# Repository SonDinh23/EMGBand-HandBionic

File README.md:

# ✋ EMGBand - Hand Bionic

<p align="center">
	<br>
	<strong>Muscle intent in → bionic motion out.</strong>   
</p>

<p align="center">
	
	&nbsp;
	
</p>

EMGBand / Hand Bionic is a full-stack, open hardware kit that turns forearm muscle signals into predictable, servo-safe hand motion. It is built to be hackable, reproducible, and fast to demo: one bill of materials, one firmware pair (ring + hand), one Flutter app to calibrate and ship.

Designed for makers, researchers, and product teams, EMGBand focuses on reliability, safety, and repeatability. The repo bundles manufacturing-ready assets (Gerbers, BOMs), production photos, a tested ESP32 firmware pair, and a Flutter app that makes calibration and demos straightforward.

## Table of Contents
- 🔍 [What this repo delivers](#what-this-repo-delivers)
- 🖼️ [Quick gallery](#quick-gallery)
- 🧭 [Platform at a glance](#platform-at-a-glance)
- ⚙️ [Architecture snapshot](#architecture-snapshot)
- 📚 [Deep dives](#deep-dives)
- 🚀 [Fast start](#fast-start)
- ✨ [Tech highlights](#tech-highlights)
- 📜 [Licence](#licence)
- 🙏 [Thanks](#thanks)

| | | |
| --- | --- | --- |
|  |  |  |

<p align="center"><sub>Wearable EMG ring + controller blocks from the latest build.</sub></p>

## What this repo delivers
- **Hardware you can fabricate**: KiCad projects for the MyoBand EMG front-end, hand controller, and modular sensor blocks. Gerbers, pick-and-place, and reference photos are ready for a quick manufacturing turn.
- **Firmware that guards the hardware**: ESP32 (ring + hand) stack with EMG filtering, intent classification, BLE services, OTA hooks, and stall-safe servo control so experiments stay repeatable and safe.
- **App that closes the loop**: Flutter client to scan, pair, stream EMG, calibrate thresholds (Line/Radar), push configs, and swap control modes without reflashing.
- **Media to build confidence**: Photos and demo videos to set assembly expectations before you order or solder.

## Quick gallery

See how the wearable comes together before diving into schematics or code.

| | | |
| --- | --- | --- |
| <br><small>📸 Assembled unit 1</small> | <br><small>📸 Assembled unit 2</small> | <br><small>📸 Assembled unit 3</small> |
| <br><small>🖼️ Side profile</small> | <br><small>🔬 Sensor block close-up</small> | <br><small>🔗 Strap view</small> |

<p align="center"><strong>Live demo videos</strong></p>
<p align="center">
	<video src="resources/video/Demo1.mp4" width="360" controls muted></video>
	<video src="resources/video/Demo2.mp4" width="360" controls muted></video>
</p>

<p align="center"><small>If embeds do not autoplay in your viewer, use the direct links: <a href="resources/video/Demo1.mp4">Demo1.mp4</a> · <a href="resources/video/Demo2.mp4">Demo2.mp4</a>.</small></p>

## Platform at a glance

| Layer | Highlights |
| --- | --- |
| 🛠️ **Hardware** | Low-noise EMG front-end, modular controller blocks, ready-to-manufacture assets, BOMs aligned to the photos you see. |
| 🧠 **Firmware** | ESP32 (ring + hand), FreeRTOS, NimBLE, OTA-ready, Line/Radar classifiers, servo current and motion guards to avoid stalls. |
| 📱 **App** | Flutter UX for BLE JSON control, half-float EMG streaming, auto pair/connect, per-user calibration, and live plots. |

## Architecture snapshot

Signal path in two stages: capture and clean EMG on the ring, classify intent and drive actuators on the hand controller. Calibration data lives in the app and syncs over BLE when you change modes.

<table>
	<tr>
		<td align="center"><br><small>⚡ Raw EMG capture</small></td>
			<td align="center"><br><small>🔎 Line thresholds</small></td>
			<td align="center"><br><small>🔁 Radar/Spider matching</small></td>
	</tr>
	<tr>
		<td align="center"><br><small>✅ Match confidence</small></td>
		<td align="center"><br><small>➖ Similarity metric</small></td>
		<td align="center"><br><small>📱 Flutter app in action</small></td>
	</tr>
</table>

## Deep dives
- Hardware overview, IC map, and board variants: [hardware/README.md](hardware/README.md)
- Firmware flow, EMG filters/classifiers, BLE/OTA services: [firmware/README.md](firmware/README.md)
- App BLE flows, JSON protocol, half-float decode, and UI cues: [app/README.md](app/README.md)

## Fast start
1) **Fabricate / assemble**: pick your board set from [hardware](hardware/README.md); use the included Gerbers and assembly files to keep builds consistent with the photos.
2) **Flash firmware**: open `firmware/Embedded` in VS Code + PlatformIO, select the target (ring/hand), and run `pio run -t upload`.
3) **Pair with the app**: run the Flutter app (see [app/README.md](app/README.md)), scan and save Hand + MyoBand, then start EMG streaming.
4) **Calibrate deliberately**: choose Line or Radar, adjust thresholds/templates, push to devices, and watch the live plots to confirm stability.
5) **Demo safely**: use the stall/over-activity protections while you tune grip strength or motion ranges.

## Tech highlights
- Half-precision EMG streaming keeps BLE lean; float32 reconstruction happens in the app for analysis.
- Dual control modes: Line (summed thresholds for fast response) and Radar/Spider (template similarity, ≥70% match) for finer intent mapping.
- Safety nets: relax-before-use gating, over-activity clamps, current-based stall detection on servos, watchdog-backed tasks, and OTA hooks for quick fixes.
- UX polish: LED/buzzer cues, auto reconnect, smoothed charts, per-grip calibration profiles, and JSON-based control that is easy to script.

## Licence

This project is licensed under the GNU GPLv3.  
Compared to permissive licences like MIT, GPLv3 requires that if you modify this code and distribute your version (including in commercial products), you must also release your changes under the same GPLv3 licence and provide the corresponding source code.  

This way, everyone can benefit from improvements built on top of this project.  
If this licence causes issues for your intended use, feel free to contact me – I’m open to discussing alternatives.

## Thanks

Huge thanks to contributors, early testers, and the open-source toolchains that made this build possible. Enjoy hacking, and share what you build.

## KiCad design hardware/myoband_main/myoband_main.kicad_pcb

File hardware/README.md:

# 🔧 Hardware Reference

The definitive pit stop for every PCB in the EMGBand/Hand Bionic stack. Each section tells you what the board does, how it talks to the rest, where to grab build assets, and what to check before you power it up—plus a gallery pulled straight from the committed files.

## 📌 At-a-glance

| Board | Role | Primary interfaces | Manufacturing kit |
| --- | --- | --- | --- |
| [Hand_main](#hand_main) | Bionic hand controller, Wi-Fi/BLE, power/rail monitor | USB-C, UART, GPIO, RGB LED | `Hand_main/*.kicad_*`, top/bottom photos |
| [myoband_main](#myoband_main) | Wearable hub for EMG/IMU/mic, power + comms | USB-UART, Wi-Fi/BLE, SPI/I2C/I2S, ADC | `myoband_main/*.kicad_*`, top/bottom photos |
| [myoBand_emg](#myoBand_emg) | EMG front-end with INA333 multi-stage filtering | Differential electrodes → analog out | `myoBand_emg/*.kicad_*`, top/bottom photos |
| [myoBand_emg_Renesas v0.2](#myoBand_emg_renesas-v02) | EMG front-end using ISL28533 | Differential electrodes → analog out | `myoBand_emg_Renesas/myoBand_emg_v0_2/*.kicad_*` |
| [myoBand_emg_Simulation](#myoBand_emg_simulation) | EMG filter/response simulation | N/A (SPICE) | `myoBand_emg_Simulation/*.kicad_*` |

---

## 🧠 Hand_main

### Highlights
- ESP32-WROOM-32D brain with Wi-Fi/BLE and a status RGB LED to keep you informed at a glance.
- INA3221 keeps eyes on three rails, so servos and external loads stay within safe current/voltage envelopes.
- TPS54620 buck + XC6220 LDO make clean rails; CP2102N USB–UART streamlines flashing and debug.

### Quick specs

| Parameter | Detail |
| --- | --- |
| MCU | ESP32-WROOM-32D |
| Power | Buck 5V→system, 3V3 LDO |
| Power monitor | INA3221 (3 channels) |
| Interfaces | USB-C/CP2102N, GPIO headers, WS2812 data |

### Manufacturing files
- [Hand_main/Hand_main.kicad_sch](Hand_main/Hand_main.kicad_sch)
- [Hand_main/Hand_main.kicad_pcb](Hand_main/Hand_main.kicad_pcb)
- [Hand_main/Hand_main.pdf](Hand_main/Hand_main.pdf)

### Build & test checklist
- Double-check buck polarity and place L/C exactly as laid out to keep EMI tame.
- Probe buck and 3V3 rails before seating the ESP32 or any sensitive loads.
- Confirm USB-C orientation/UART lines, then sanity-check INA3221 readings with a dummy load.

### Gallery

<table>
	<tr>
		<td align="center"><br><small>Top — overview</small></td>
		<td align="center"><br><small>Top — ESP32 & power</small></td>
	</tr>
	<tr>
		<td align="center"><br><small>Bottom — routing</small></td>
		<td align="center"><br><small>Bottom — pours</small></td>
	</tr>
</table>

---

## 🧭 myoband_main

### Highlights
- ESP32-PICO-V3-02 wearable hub that ingests EMG (MCP3208), IMU data (LSM6DSL), and PDM audio (INMP441).
- Power spine: TP4056 Li-ion charger, 3V3 LDO for logic, TPS60402 negative rail for the analog front-end.
- CP2102N handles flashing/debug; WS2812B-2020 signals state; headers expose SPI/I2C/I2S for expansions.

### Quick specs

| Parameter | Detail |
| --- | --- |
| MCU | ESP32-PICO-V3-02 |
| EMG conversion | MCP3208 (12-bit SPI) |
| Sensors | IMU LSM6DSL, mic INMP441 |
| Power | TP4056 charger, 3V3 LDO, TPS60402 negative rail |
| Interfaces | Wi-Fi/BLE, USB-UART, SPI/I2C/I2S, GPIO |

### Manufacturing files
- [myoband_main/myoband_main.kicad_sch](myoband_main/myoband_main.kicad_sch)
- [myoband_main/myoband_main.kicad_pcb](myoband_main/myoband_main.kicad_pcb)
- [myoband_main/myoband_main.pdf](myoband_main/myoband_main.pdf)

### Build & test checklist
- Inspect TP4056 charge path and battery polarity; watch thermals at higher charge currents.
- Verify the TPS60402 negative rail before biasing the EMG analog stage.
- Smoke-test everything together: Wi-Fi/BLE, SPI EMG ADC, I2C IMU, PDM mic—and listen for noise coupling.

### Gallery

<table>
	<tr>
		<td align="center"><br><small>Top — overview</small></td>
		<td align="center"><br><small>Top — MCU & IO</small></td>
		<td align="center"><br><small>Top — power/charger</small></td>
	</tr>
	<tr>
		<td align="center"><br><small>Bottom — routing</small></td>
		<td align="center"><br><small>Bottom — pours</small></td>
		<td align="center"><br><small>Bottom — placement</small></td>
	</tr>
</table>

---

## 🩺 myoBand_emg (INA333)

### Highlights
- INA333-based EMG front-end for low-noise differential gain, feeding MCP601 stages for band-pass/notch shaping.
- TPS60402 negative rail preserves headroom and keeps distortion low at higher amplitudes.
- Layout favors short electrode runs and clean analog planes away from digital chatter.

### Quick specs

| Parameter | Detail |
| --- | --- |
| Instrumentation amp | INA333 |
| Filter op-amp | MCP601 (multi-stage) |
| Power | Negative rail via TPS60402, bias/offset via R/C network |
| Output | Analog to ADC (e.g., MCP3208 on myoband_main) |

### Manufacturing files
- [myoBand_emg/EMG_SENSOR.kicad_sch](myoBand_emg/EMG_SENSOR.kicad_sch)
- [myoBand_emg/EMG_SENSOR.kicad_pcb](myoBand_emg/EMG_SENSOR.kicad_pcb)
- [myoBand_emg/EMG_SENSOR.pdf](myoBand_emg/EMG_SENSOR.pdf)

### Build & test checklist
- Match R/C values to your target corners; confirm INA333 orientation and gain resistors.
- Measure the negative rail before attaching electrodes; verify mid-bias to avoid clipping.
- Characterize baseline noise; notch the mains band or add ferrites if hum shows up.

### Gallery

<table>
	<tr>
		<td align="center"><br><small>Top — overview</small></td>
		<td align="center"><br><small>Top — amp/filter</small></td>
	</tr>
	<tr>
		<td align="center"><br><small>Bottom — routing</small></td>
		<td align="center"><br><small>Bottom — pours</small></td>
	</tr>
</table>

---

## 🩺 myoBand_emg_Renesas v0.2 (ISL28533)

### Highlights
- Renesas ISL28533 variant for a broader dynamic range and lower noise floor.
- MCP601 stack still handles staged gain and filtering; rails/bias come from the hub via R/C network.
- Same disciplined layout: short electrode routes, isolated analog plane, test-points where you need them.

### Quick specs

| Parameter | Detail |
| --- | --- |
| Instrumentation amp | ISL28533 |
| Filter op-amp | MCP601 |
| Power | Rails/bias from hub or external (no onboard charge pump) |
| Output | Analog to hub ADC |

### Manufacturing files
- [myoBand_emg_Renesas/myoBand_emg_v0_2/myoBand_emg_v0_2.kicad_sch](myoBand_emg_Renesas/myoBand_emg_v0_2/myoBand_emg_v0_2.kicad_sch)
- [myoBand_emg_Renesas/myoBand_emg_v0_2/myoBand_emg_v0_2.kicad_pcb](myoBand_emg_Renesas/myoBand_emg_v0_2/myoBand_emg_v0_2.kicad_pcb)
- [myoBand_emg_Renesas/myoBand_emg_v0_2/myoBand_emg_v0_2.pdf](myoBand_emg_Renesas/myoBand_emg_v0_2/myoBand_emg_v0_2.pdf)

### Build & test checklist
- Validate mid-rail bias when powered from the hub; confirm ISL28533 headroom at your chosen gain.
- A/B noise against the INA333 build to choose the production winner.
- Drop in renders/photos once assembled to lock placement confidence.

### Gallery
- No images in this folder yet; drop in PNG/JPG renders or photos when ready.

---

## 🧪 myoBand_emg_Simulation

### Highlights
- SPICE sandbox to shape EMG gain and filter response before you spend copper.
- Ideal sources and R/C only—no production silicon here.

### Quick specs

| Parameter | Detail |
| --- | --- |
| Purpose | Frequency/gain/notch simulation |
| Components | Ideal sources, R/C |
| Output | Simulated waveforms |

### Files
- [myoBand_emg_Simulation/myoBand_emg_Simulation.kicad_sch](myoBand_emg_Simulation/myoBand_emg_Simulation.kicad_sch)
- [myoBand_emg_Simulation/myoBand_emg_Simulation.kicad_pcb](myoBand_emg_Simulation/myoBand_emg_Simulation.kicad_pcb)

---

## 🖼️ Image & path guidance

- Use forward slashes `/` in image paths; links are relative to this README.
- Example: ``.
- GitHub renders images once the PNG files are present; add new renders/photos in the matching board folder.
- Prefer per-board READMEs or a PDF gallery? Say the word and we will scaffold it.

---

_Last refreshed: check git history for the latest author/date._

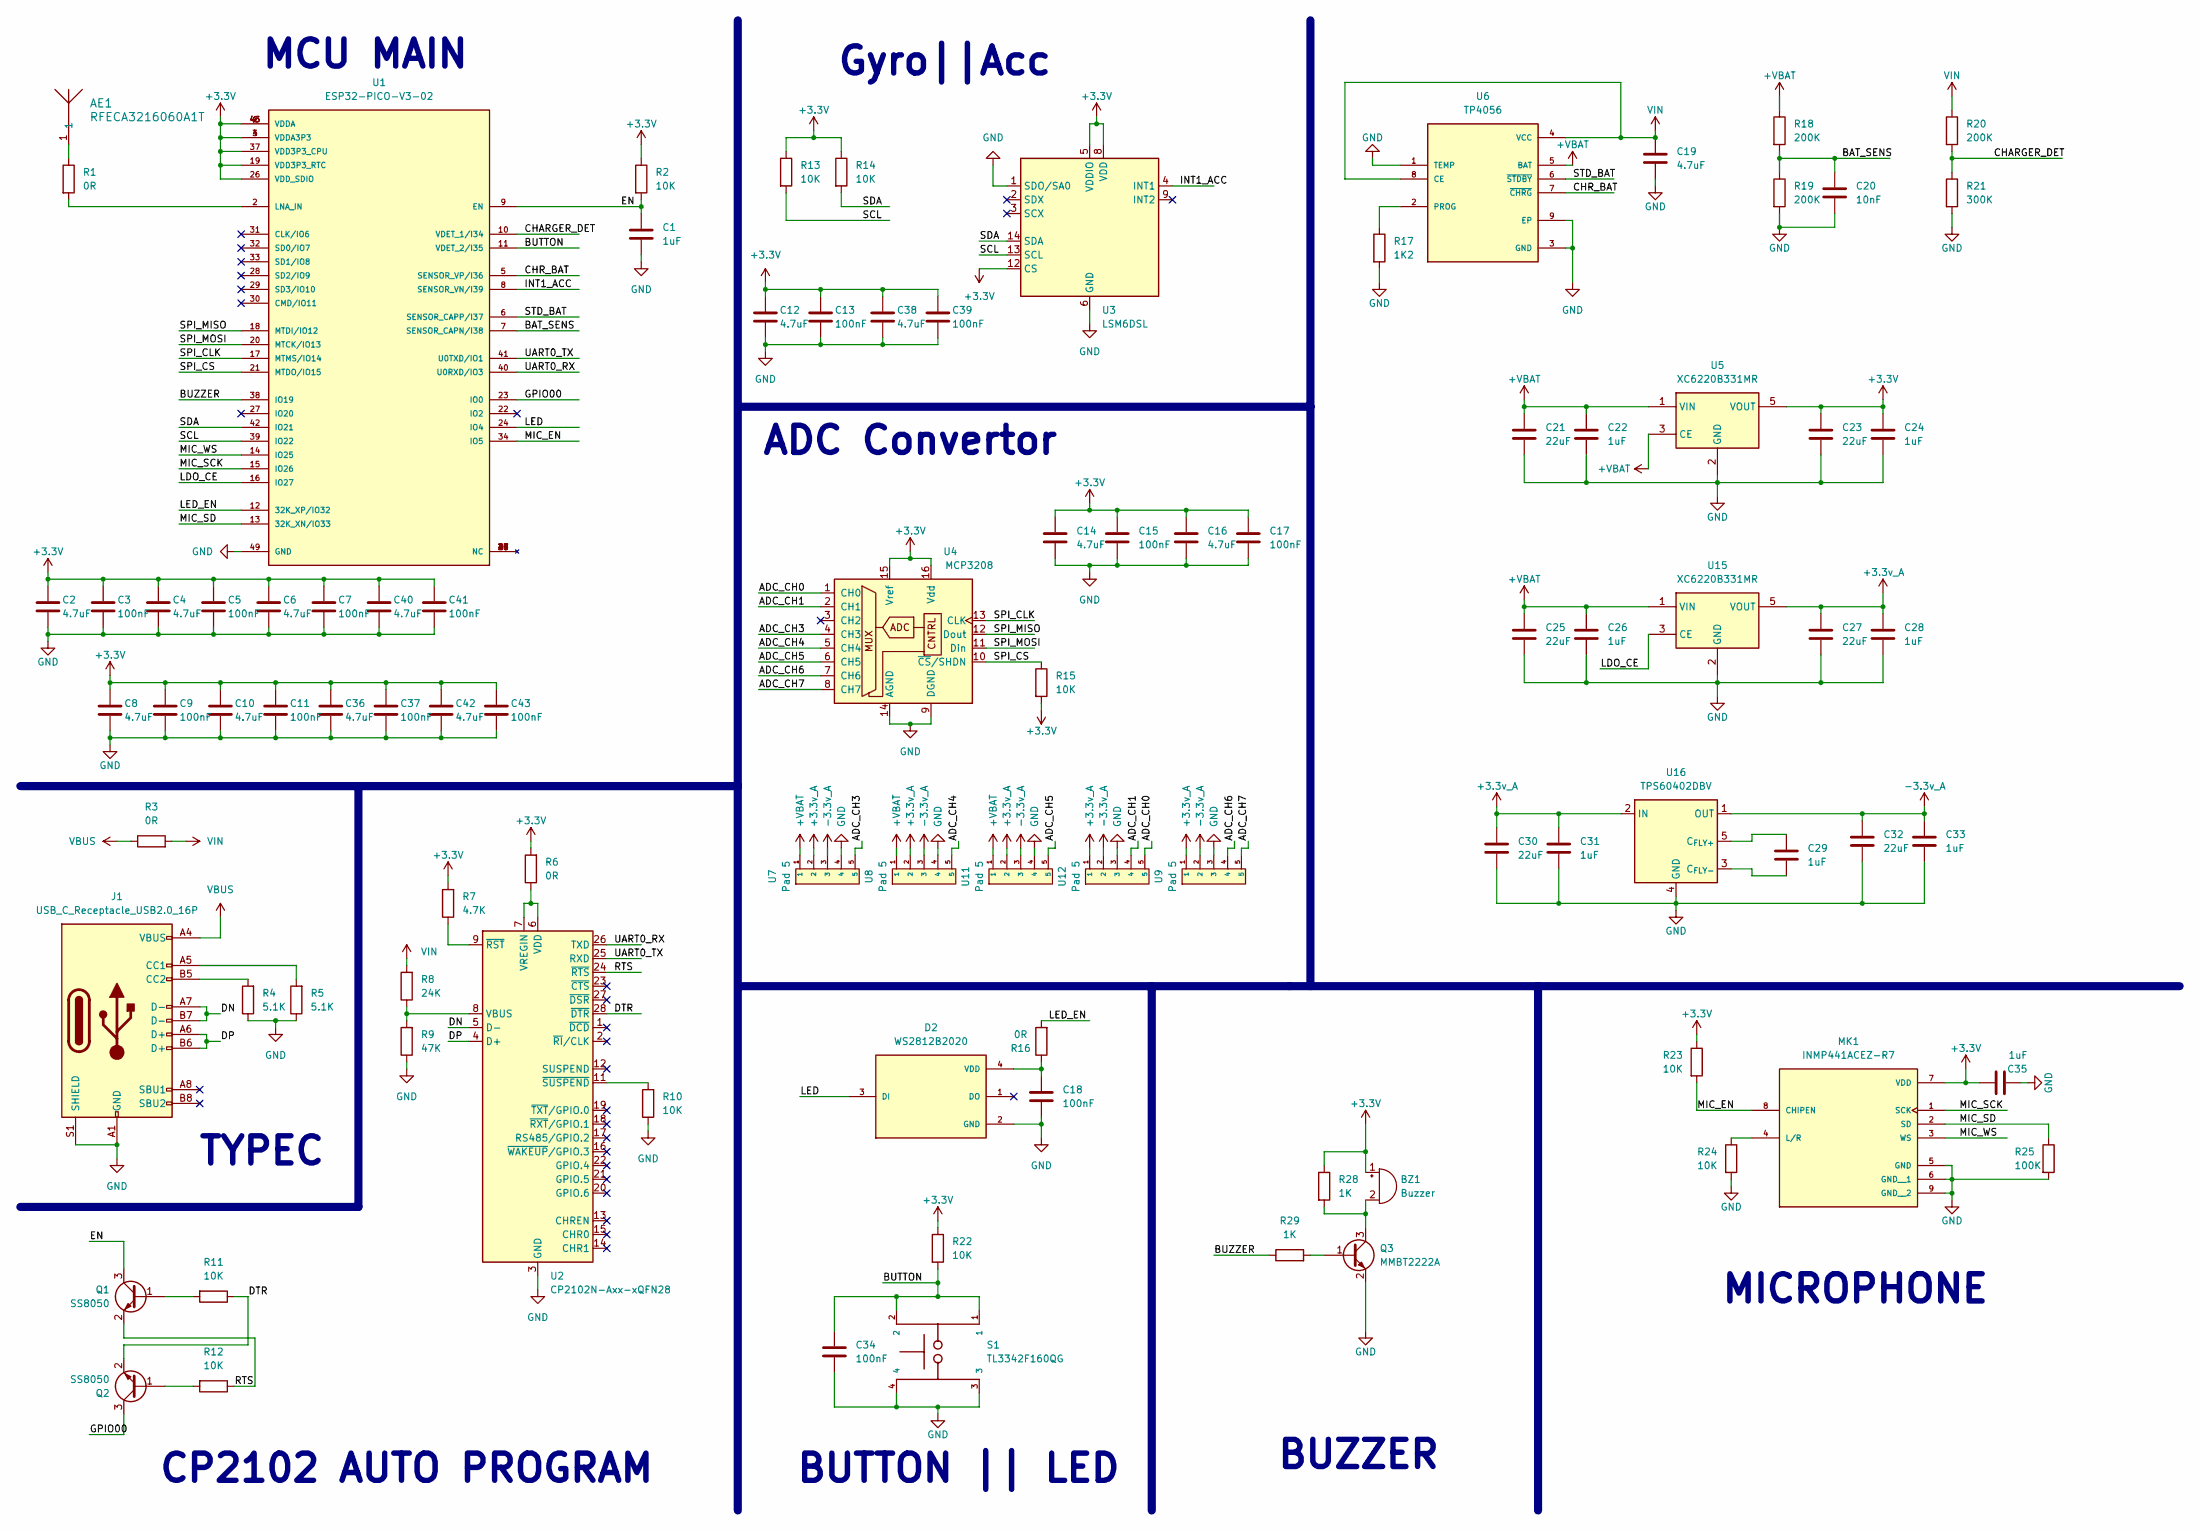
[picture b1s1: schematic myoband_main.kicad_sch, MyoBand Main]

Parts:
AE1: RFECA3216060A1T; ANT_16060A1T_WAL
BZ1: Buzzer; Buzzer_Murata_PKMCS0909E
C1, C22, C24, C26, C28, C29, C31, C33, C35: 1uF; C_0402_1005Metric
C2, C4, C6, C8, C10, C12, C14, C16, C19, C36, C38, C40, C42: 4.7uF; C_0402_1005Metric
C3, C5, C7, C9, C11, C13, C15, C17, C18, C34, C37, C39, C41, C43: 100nF; C_0402_1005Metric
C20: 10nF; C_0402_1005Metric
C21, C23, C25, C27, C30, C32: 22uF; C_0603_1608Metric
D2: WS2812B2020; LED_WS2812B2020; PARTREV V1.0
J1: USB_C_Receptacle_USB2.0_16P; USB_C_Receptacle_GCT_USB4105-xx-A_16P_TopMnt_Horizontal
MK1: INMP441ACEZ-R7; MIC_INMP441ACEZ-R7; PARTREV 1.1
Q1, Q2: SS8050; SOT-23
Q3: MMBT2222A; SOT-23
R1, R3, R6, R16: 0R; C_0402_1005Metric
R2, R10, R11, R12, R13, R14, R15, R22, R23, R24: 10K; C_0402_1005Metric
R4, R5: 5.1K; C_0402_1005Metric
R7: 4.7K; C_0402_1005Metric
R8: 24K; C_0402_1005Metric
R9: 47K; C_0402_1005Metric
R17: 1K2; C_0402_1005Metric
R18, R19, R20: 200K; C_0402_1005Metric
R21: 300K; C_0402_1005Metric
R25: 100K; C_0402_1005Metric
R28, R29: 1K; C_0402_1005Metric
S1: TL3342F160QG; SW_TL3342F160QG
U1: ESP32-PICO-V3-02; XCVR_ESP32-PICO-V3-02; PARTREV 1.0
U2: CP2102N-Axx-xQFN28; QFN-28-1EP_5x5mm_P0.5mm_EP3.35x3.35mm
U3: LSM6DSL; LGA-14_3x2.5mm_P0.5mm_LayoutBorder3x4y
U4: MCP3208; SOIC-16_3.9x9.9mm_P1.27mm
U5, U15: XC6220B331MR; SOT-23-5
U6: TP4056; SOP127P600X175-9N
U7, U8, U9, U11, U12: Pad 5
U16: TPS60402DBV; SOT-23-5

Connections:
+3.3V: BZ1.1 (+), C2.1, C3.1, C4.1, C5.1, C6.1, C7.1, C8.1, C9.1, C10.1, C11.1, C12.1, C13.1, C14.1, C15.1, C16.1, C17.1, C23.1, C24.1, C35.1, C36.1, C37.1, C38.1, C39.1, C40.1, C41.1, C42.1, C43.1, MK1.7 (VDD), R2.1, R6.2, R7.2, R13.1, R14.1, R15.2, R22.1, R23.1, R28.1, U1.1 (VDDA), U1.3 (VDDA3P3), U1.4 (VDDA3P3), U1.19 (VDD3P3_RTC), U1.26 (VDD_SDIO), U1.37 (VDD3P3_CPU), U1.43 (VDDA), U1.46 (VDDA), U3.5 (VDDIO), U3.8 (VDD), U3.12 (CS), U4.15 (Vref), U4.16 (Vdd), U5.5 (VOUT)
+3.3v_A: C27.1, C28.1, C30.1, C31.1, U7.2, U8.2, U9.1, U11.2, U12.1, U15.5 (VOUT), U16.2 (IN)
+VBAT: C21.1, C22.1, C25.1, C26.1, R18.1, U5.1 (VIN), U5.3 (CE), U6.5 (BAT), U7.1, U8.1, U11.1, U15.1 (VIN)
-3.3v_A: C32.1, C33.1, U7.3, U8.3, U9.2, U11.3, U12.2, U16.1 (OUT)
/ADC_CH0: U4.1 (CH0), U12.5
/ADC_CH1: U4.2 (CH1), U12.4
/ADC_CH3: U4.4 (CH3), U7.5
/ADC_CH4: U4.5 (CH4), U8.5
/ADC_CH5: U4.6 (CH5), U11.5
/ADC_CH6: U4.7 (CH6), U9.4
/ADC_CH7: U4.8 (CH7), U9.5
/BAT_SENS: C20.1, R18.2, R19.1, U1.7 (SENSOR_CAPN/I38)
/BUTTON: C34.1, R22.2, S1.1, S1.2, U1.11 (VDET_2/I35)
/BUZZER: R29.1, U1.38 (IO19)
/CHARGER_DET: R20.2, R21.1, U1.10 (VDET_1/I34)
/CHR_BAT: U1.5 (SENSOR_VP/I36), U6.7 (~CHRG)
/DN: J1.A7 (D-), J1.B7 (D-), U2.5 (D-)
/DP: J1.A6 (D+), J1.B6 (D+), U2.4 (D+)
/DTR: Q2.2 (E), R11.1, U2.28 (~DTR)
/EN: C1.1, Q1.3 (C), R2.2, U1.9 (EN)
/GPIO00: Q2.3 (C), U1.23 (IO0)
/INT1_ACC: U1.8 (SENSOR_VN/I39), U3.4 (INT1)
/LDO_CE: U1.16 (IO27), U15.3 (CE)
/LED: D2.3 (DI), U1.24 (IO4)
/LED_EN: R16.2, U1.12 (32K_XP/IO32)
/MIC_EN: MK1.8 (CHIPEN), R23.2, U1.34 (IO5)
/MIC_SCK: MK1.1 (SCK), U1.15 (IO26)
/MIC_SD: MK1.2 (SD), R25.1, U1.13 (32K_XN/IO33)
/MIC_WS: MK1.3 (WS), U1.14 (IO25)
/RTS: Q1.2 (E), R12.1, U2.24 (~RTS)
/SCL: R13.2, U1.39 (IO22), U3.13 (SCL)
/SDA: R14.2, U1.42 (IO21), U3.14 (SDA)
/SPI_CLK: U1.17 (MTMS/IO14), U4.13 (CLK)
/SPI_CS: R15.1, U1.21 (MTDO/IO15), U4.10 (~CS/SHDN)
/SPI_MISO: U1.18 (MTDI/IO12), U4.12 (Dout)
/SPI_MOSI: U1.20 (MTCK/IO13), U4.11 (Din)
/STD_BAT: U1.6 (SENSOR_CAPP/I37), U6.6 (~STDBY)
/UART0_RX: U1.40 (U0RXD/IO3), U2.26 (TXD)
/UART0_TX: U1.41 (U0TXD/IO1), U2.25 (RXD)
GND: C1.2, C2.2, C3.2, C4.2, C5.2, C6.2, C7.2, C8.2, C9.2, C10.2, C11.2, C12.2, C13.2, C14.2, C15.2, C16.2, C17.2, C18.2, C19.2, C20.2, C21.2, C22.2, C23.2, C24.2, C25.2, C26.2, C27.2, C28.2, C30.2, C31.2, C32.2, C33.2, C34.2, C35.2, C36.2, C37.2, C38.2, C39.2, C40.2, C41.2, C42.2, C43.2, D2.2 (GND), J1.A1 (GND), J1.A12 (GND), J1.B1 (GND), J1.B12 (GND), J1.S1 (SHIELD), MK1.5 (GND), MK1.6 (GND__1), MK1.9 (GND__2), Q3.2 (E), R4.1, R5.1, R9.1, R10.1, R17.2, R19.2, R21.2, R24.2, R25.2, S1.3, S1.4, U1.49 (GND), U2.3 (GND), U2.29 (GND), U3.1 (SDO/SA0), U3.6 (GND), U3.7 (GND), U4.9 (DGND), U4.14 (AGND), U5.2 (GND), U6.1 (TEMP), U6.3 (GND), U6.9 (EP), U7.4, U8.4, U9.3, U11.4, U12.3, U15.2 (GND), U16.4 (GND)
unnamed: AE1.1, R1.1
unnamed: BZ1.2 (-), Q3.3 (C), R28.2
unnamed: C18.1, D2.4 (VDD), R16.1
unnamed: J1.A5 (CC1), R5.2
unnamed: J1.B5 (CC2), R4.2
unnamed: MK1.4 (L/R), R24.1
unnamed: Q1.1 (B), R11.2
unnamed: Q2.1 (B), R12.2
unnamed: Q3.1 (B), R29.2
unnamed: R1.2, U1.2 (LNA_IN)
unnamed: R8.1, R9.2, U2.8 (VBUS)
unnamed: R6.1, U2.6 (VDD), U2.7 (VREGIN)
unnamed: R7.1, U2.9 (~RST)
unnamed: R10.2, U2.11 (~SUSPEND)
unnamed: R17.1, U6.2 (PROG)
unnamed: C29.1, U16.5 (C_{FLY+})
unnamed: C29.2, U16.3 (C_{FLY-})
VBUS: J1.A4 (VBUS), J1.A9 (VBUS), J1.B4 (VBUS), J1.B9 (VBUS), R3.1
VIN: C19.1, R3.2, R8.2, R20.1, U6.4 (VCC), U6.8 (CE)

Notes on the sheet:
MCU MAIN
TYPEC
BUTTON || LED
Gyro||Acc
MICROPHONE
CP2102 AUTO PROGRAM
BUZZER
ADC Convertor

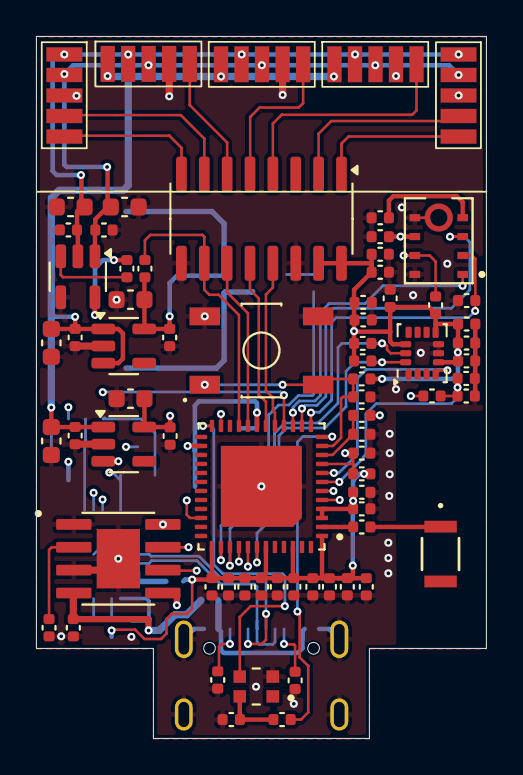
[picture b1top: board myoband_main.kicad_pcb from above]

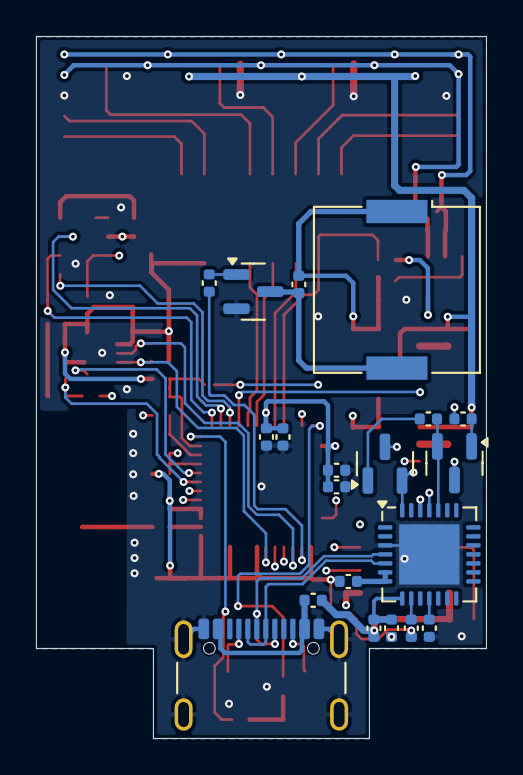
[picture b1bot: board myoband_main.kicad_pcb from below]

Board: 4 copper layers, 25.0 x 39.0 mm, 92 parts (20 on the bottom side), 59 nets.

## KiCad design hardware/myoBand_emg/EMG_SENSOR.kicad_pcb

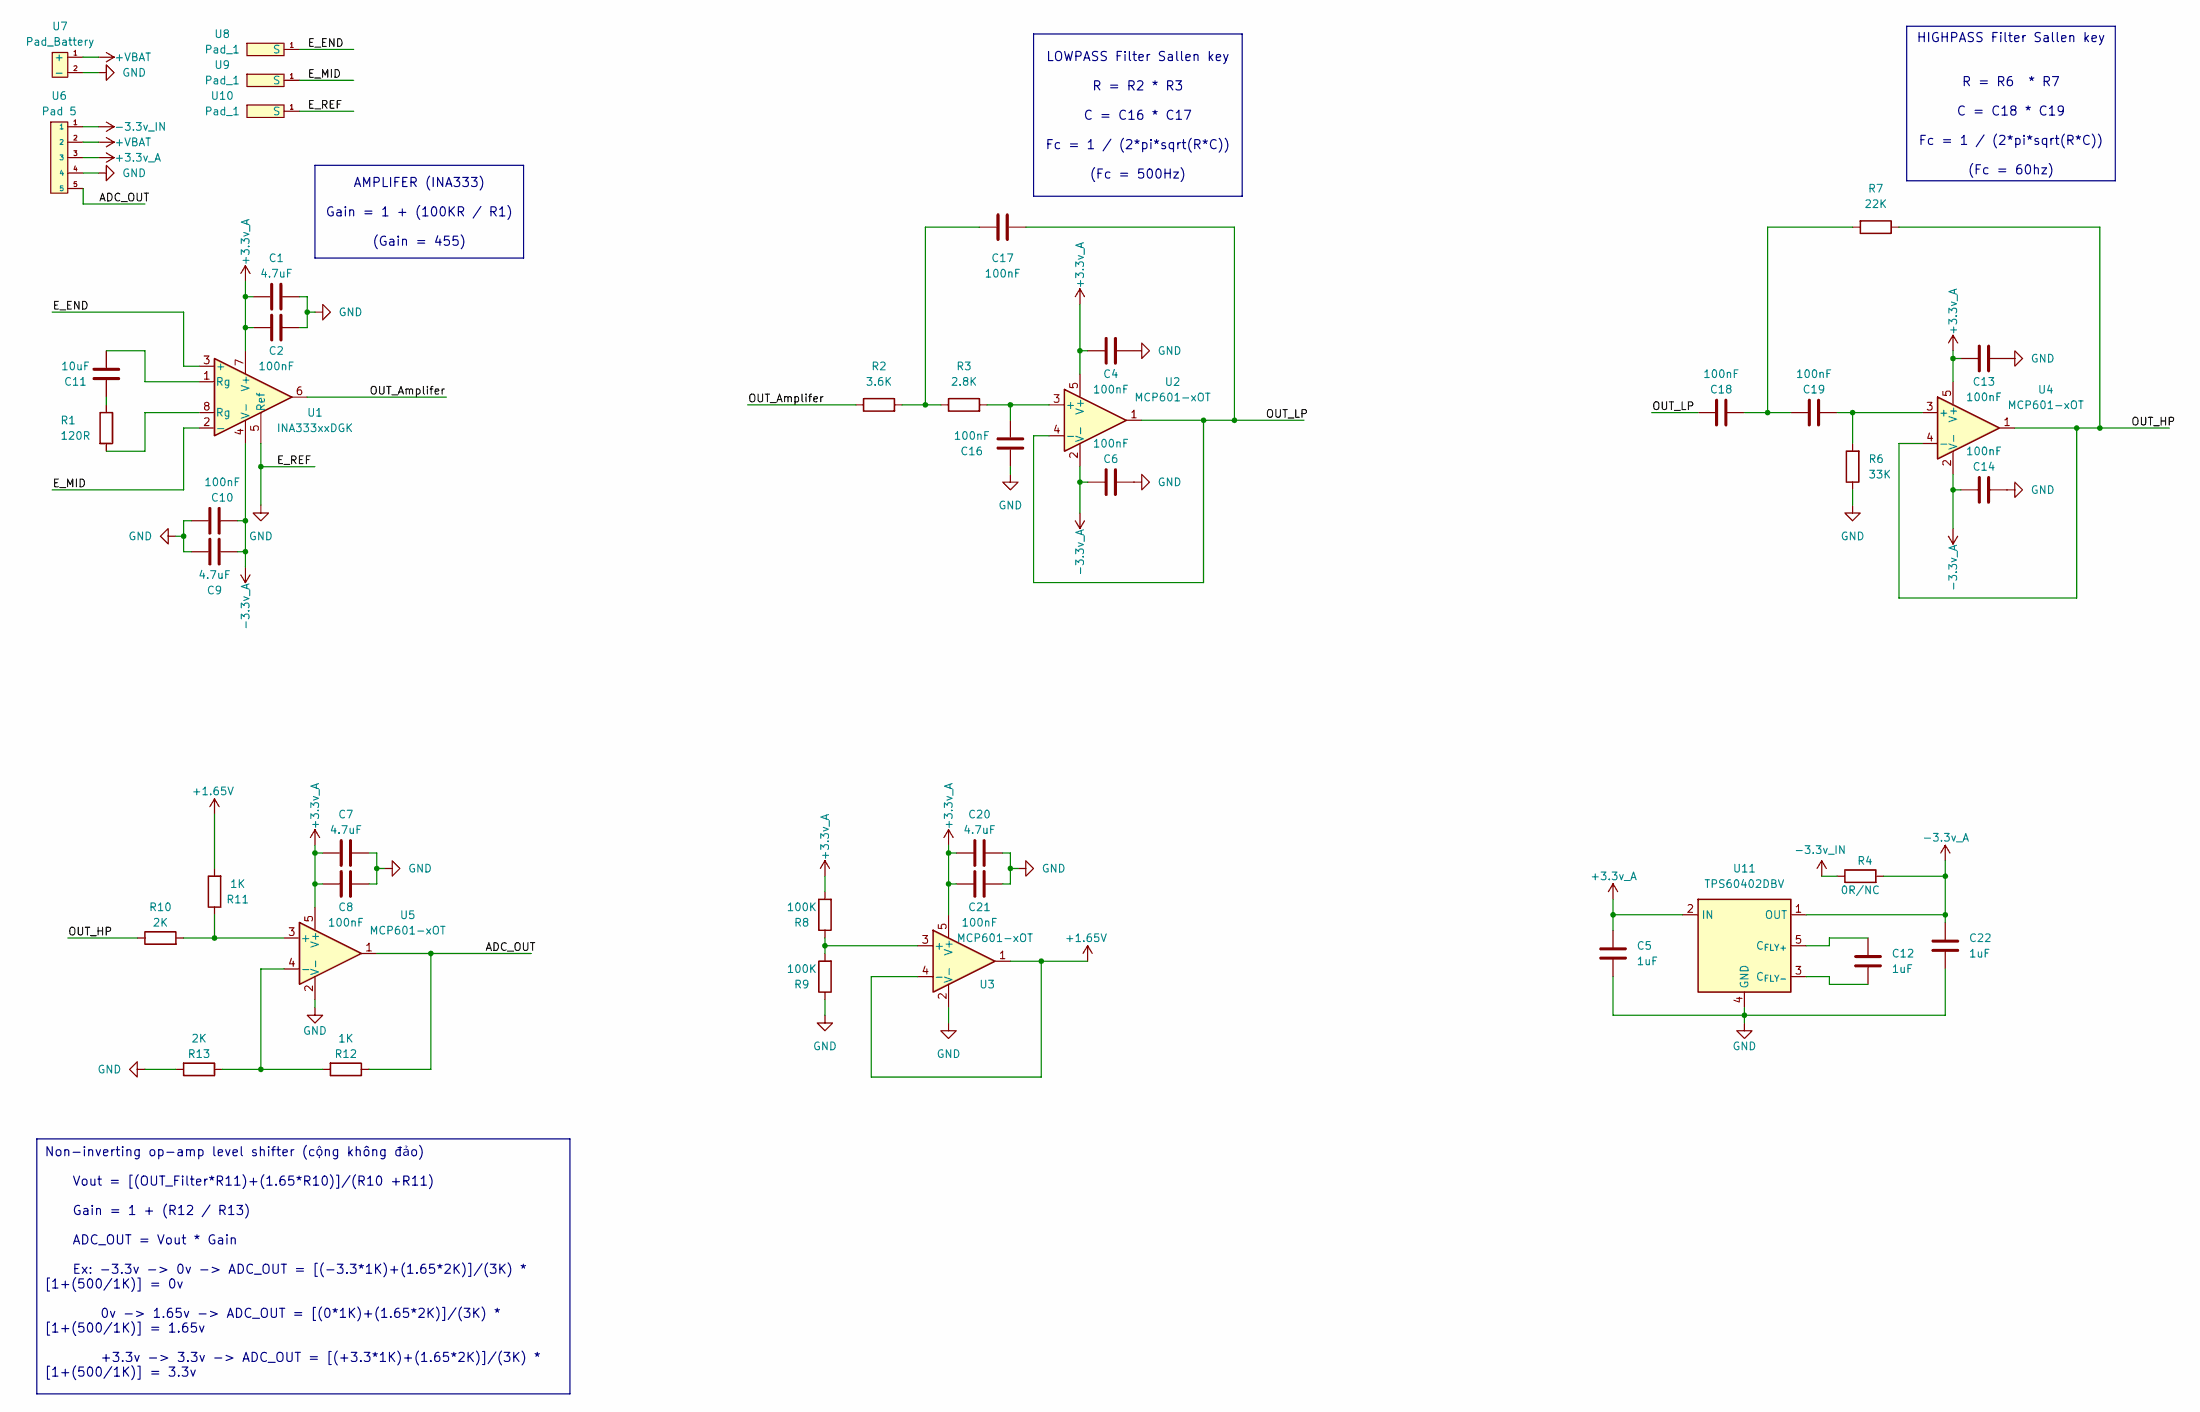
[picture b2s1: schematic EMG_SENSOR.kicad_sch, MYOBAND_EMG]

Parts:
C1, C7, C9, C20: 4.7uF; C_0402_1005Metric
C2, C4, C6, C8, C10, C13, C14, C16, C17, C18, C19, C21: 100nF; C_0402_1005Metric
C5, C12, C22: 1uF; C_0402_1005Metric
C11: 10uF; C_0603_1608Metric
R1: 120R; R_0402_1005Metric
R2: 3.6K; R_0402_1005Metric
R3: 2.8K; R_0402_1005Metric
R4: 0R/NC; R_0402_1005Metric
R6: 33K; R_0402_1005Metric
R7: 22K; R_0402_1005Metric
R8, R9: 100K; R_0402_1005Metric
R10, R13: 2K; R_0402_1005Metric
R11, R12: 1K; R_0402_1005Metric
U1: INA333xxDGK; VSSOP-8_3x3mm_P0.65mm
U2, U3, U4, U5: MCP601-xOT; SOT-23-5_HandSoldering
U6: Pad 5
U7: Pad_Battery; Pad Battery
U8, U9, U10: Pad_1; Pad 1
U11: TPS60402DBV; SOT-23-5

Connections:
+1.65V: R11.2, U3.1, U3.4 (-)
+3.3v_A: C1.1, C2.1, C4.1, C5.1, C7.1, C8.1, C13.1, C20.1, C21.1, R8.2, U1.7 (V+), U2.5 (V+), U3.5 (V+), U4.5 (V+), U5.5 (V+), U6.3, U11.2 (IN)
+VBAT: U6.2, U7.1 (+)
-3.3v_A: C6.2, C9.1, C10.1, C14.2, C22.1, R4.2, U1.4 (V-), U2.2 (V-), U4.2 (V-), U11.1 (OUT)
-3.3v_IN: R4.1, U6.1
/ADC_OUT: R12.1, U5.1, U6.5
/E_END: U1.3 (+), U8.1 (S)
/E_MID: U1.2 (-), U9.1 (S)
/OUT_Amplifer: R2.1, U1.6
/OUT_HP: R7.1, R10.1, U4.1, U4.4 (-)
/OUT_LP: C17.1, C18.2, U2.1, U2.4 (-)
GND: C1.2, C2.2, C4.2, C5.2, C6.1, C7.2, C8.2, C9.2, C10.2, C13.2, C14.1, C16.1, C20.2, C21.2, C22.2, R6.1, R9.1, R13.2, U1.5 (Ref), U3.2 (V-), U5.2 (V-), U6.4, U7.2 (-), U10.1 (S), U11.4 (GND)
unnamed: C11.1, R1.1
unnamed: C11.2, U1.1 (Rg)
unnamed: C17.2, R2.2, R3.1
unnamed: C18.1, C19.2, R7.2
unnamed: R1.2, U1.8 (Rg)
unnamed: C16.2, R3.2, U2.3 (+)
unnamed: R8.1, R9.2, U3.3 (+)
unnamed: C19.1, R6.2, U4.3 (+)
unnamed: R10.2, R11.1, U5.3 (+)
unnamed: R12.2, R13.1, U5.4 (-)
unnamed: C12.1, U11.5 (C_{FLY+})
unnamed: C12.2, U11.3 (C_{FLY-})

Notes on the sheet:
HIGHPASS Filter Sallen key R = R6 * R7 C = C18 * C19 Fc = 1 / (2*pi*sqrt(R*C)) (Fc = 60hz)
Non-inverting op-amp level shifter (cộng không đảo) Vout = [(OUT_Filter*R11)+(1.65*R10)]/(R10 +R11) Gain = 1 + (R12 / R13) ADC_OUT = Vout * Gain Ex: -3.3v -> 0v -> ADC_OUT = [(-3.3*1K)+(1.65*2K)]/(3K) * [1+(500/1K)] = 0v 0v -> 1.65v -> ADC_OUT = [(0*1K)+(1.65*2K)]/(3K) * [1+(500/1K)] = 1.65v +3.3v 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
LOWPASS Filter Sallen key R = R2 * R3 C = C16 * C17 Fc = 1 / (2*pi*sqrt(R*C)) (Fc = 500Hz)
AMPLIFER (INA333) Gain = 1 + (100KR / R1) (Gain = 455)

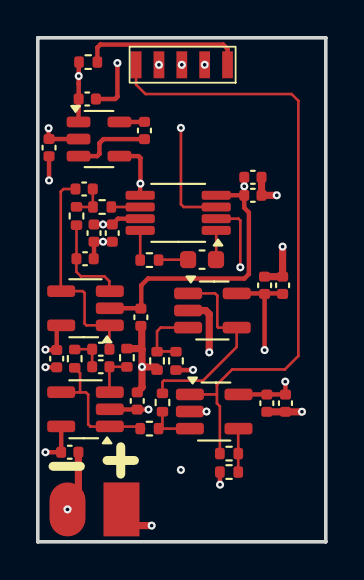
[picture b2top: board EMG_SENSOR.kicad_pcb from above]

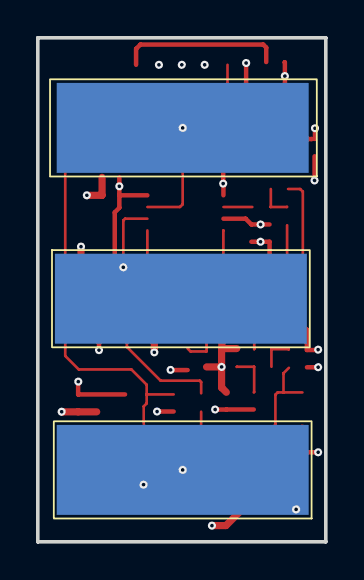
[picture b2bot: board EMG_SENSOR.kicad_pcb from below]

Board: 4 copper layers, 16.0 x 28.0 mm, 43 parts (3 on the bottom side), 24 nets.

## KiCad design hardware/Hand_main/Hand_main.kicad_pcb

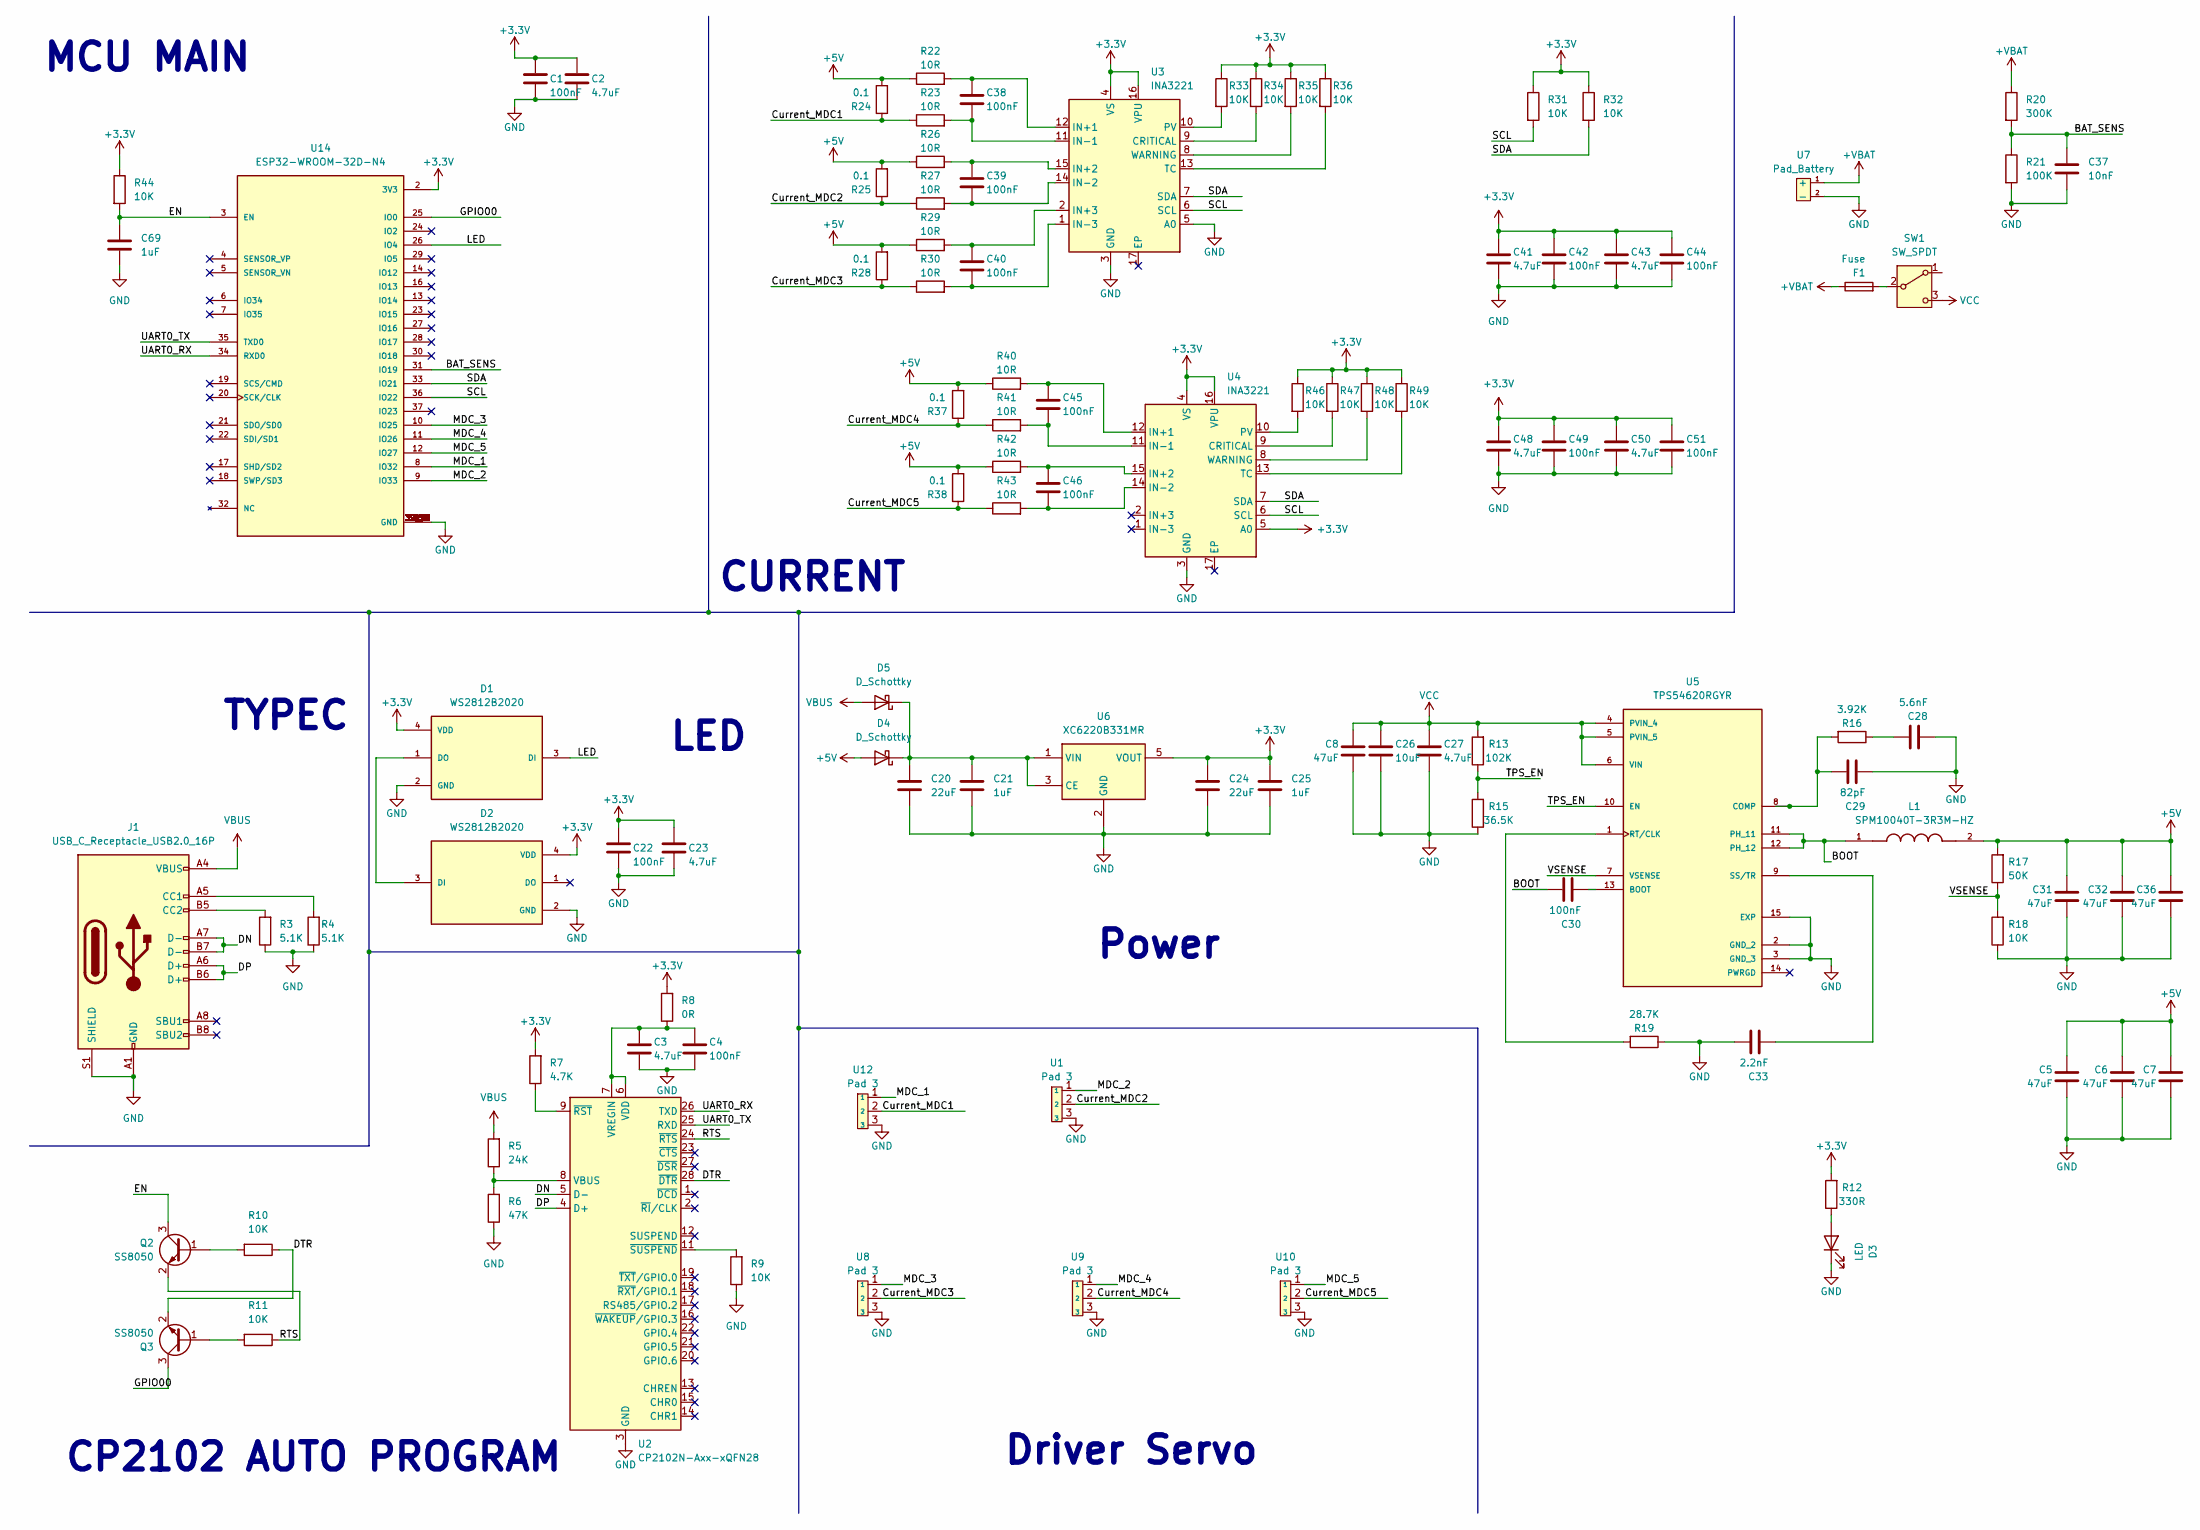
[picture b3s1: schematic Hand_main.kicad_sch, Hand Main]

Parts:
C1, C4, C22, C30, C38, C39, C40, C42, C44, C45, C46, C49, C51: 100nF; C_0402_1005Metric
C2, C3, C23, C41, C43, C48, C50: 4.7uF; C_0402_1005Metric
C5, C6, C7, C8, C31, C32, C36: 47uF; C_0805_2012Metric
C20, C24: 22uF; C_0603_1608Metric
C21, C25: 1uF; C_0603_1608Metric
C26: 10uF; C_0603_1608Metric
C27: 4.7uF; C_0603_1608Metric
C28: 5.6nF; C_0402_1005Metric
C29: 82pF; C_0402_1005Metric
C33: 2.2nF; C_0402_1005Metric
C37: 10nF; C_0402_1005Metric
C69: 1uF; C_0402_1005Metric
D1, D2: WS2812B2020; LED_WS2812B2020; PARTREV V1.0
D3: LED; LED_0805_2012Metric
D4, D5: D_Schottky; D_SOD-123
F1: Fuse; Fuse_1812_4532Metric
J1: USB_C_Receptacle_USB2.0_16P; USB_C_Receptacle_GCT_USB4105-xx-A_16P_TopMnt_Horizontal
L1: SPM10040T-3R3M-HZ; IND_SPM10040T-3R3M-HZ; PARTREV 20210512
Q2, Q3: SS8050; SOT-23
R3, R4: 5.1K; C_0402_1005Metric
R5: 24K; C_0402_1005Metric
R6: 47K; C_0402_1005Metric
R7: 4.7K; C_0402_1005Metric
R8: 0R; C_0402_1005Metric
R9, R10, R11, R18, R31, R32, R33, R34, R35, R36, R44, R46, R47, R48, R49: 10K; C_0402_1005Metric
R12: 330R; C_0402_1005Metric
R13: 102K; C_0402_1005Metric
R15: 36.5K; C_0402_1005Metric
R16: 3.92K; C_0402_1005Metric
R17: 50K; C_0402_1005Metric
R19: 28.7K; C_0402_1005Metric
R20: 300K; C_0402_1005Metric
R21: 100K; C_0402_1005Metric
R22, R23, R26, R27, R29, R30, R40, R41, R42, R43: 10R; C_0402_1005Metric
R24, R25, R28, R37, R38: 0.1; R_2512_6332Metric
SW1: SW_SPDT; SS-12D06G5
U1, U8, U9, U10, U12: Pad 3
U2: CP2102N-Axx-xQFN28; QFN-28-1EP_5x5mm_P0.5mm_EP3.35x3.35mm
U3, U4: INA3221; Texas_RGV0016A_VQFN-16-1EP_4x4mm_P0.65mm_EP2.1x2.1mm
U5: TPS54620RGYR; QFN50P350X350X100-15N; PARTREV 06/2011
U6: XC6220B331MR; SOT-23-5
U7: Pad_Battery; JST_XH_B2B-XH-AM_1x02_P2.50mm_Vertical
U14: ESP32-WROOM-32D-N4; ESP32-WROOM-32D; PARTREV 1.9

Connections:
+3.3V: C1.1, C2.1, C22.1, C23.1, C24.1, C25.1, C41.1, C42.1, C43.1, C44.1, C48.1, C49.1, C50.1, C51.1, D1.4 (VDD), D2.4 (VDD), R7.2, R8.2, R12.2, R31.1, R32.1, R33.1, R34.1, R35.1, R36.1, R44.1, R46.1, R47.1, R48.1, R49.1, U3.4 (VS), U3.16 (VPU), U4.4 (VS), U4.5 (A0), U4.16 (VPU), U6.5 (VOUT), U14.2 (3V3)
+5V: C5.2, C6.2, C7.2, C31.2, C32.2, C36.2, D4.2 (A), L1.2, R17.2, R22.1, R24.2, R25.2, R26.1, R28.2, R29.1, R37.2, R38.2, R40.1, R42.1
+VBAT: F1.1, R20.1, U7.1 (+)
/BAT_SENS: C37.1, R20.2, R21.1, U14.31 (IO19)
/BOOT: C30.1, L1.1, U5.11 (PH_11), U5.12 (PH_12)
/Current_MDC1: R23.1, R24.1, U12.2
/Current_MDC2: R25.1, R27.1, U1.2
/Current_MDC3: R28.1, R30.1, U8.2
/Current_MDC4: R37.1, R41.1, U9.2
/Current_MDC5: R38.1, R43.1, U10.2
/DN: J1.A7 (D-), J1.B7 (D-), U2.5 (D-)
/DP: J1.A6 (D+), J1.B6 (D+), U2.4 (D+)
/DTR: Q3.2 (E), R10.1, U2.28 (~DTR)
/EN: C69.1, Q2.3 (C), R44.2, U14.3 (EN)
/GPIO00: Q3.3 (C), U14.25 (IO0)
/LED: D1.3 (DI), U14.26 (IO4)
/MDC_1: U12.1, U14.8 (IO32)
/MDC_2: U1.1, U14.9 (IO33)
/MDC_3: U8.1, U14.10 (IO25)
/MDC_4: U9.1, U14.11 (IO26)
/MDC_5: U10.1, U14.12 (IO27)
/RTS: Q2.2 (E), R11.1, U2.24 (~RTS)
/SCL: R31.2, U3.6 (SCL), U4.6 (SCL), U14.36 (IO22)
/SDA: R32.2, U3.7 (SDA), U4.7 (SDA), U14.33 (IO21)
/TPS_EN: R13.1, R15.2, U5.10 (EN)
/UART0_RX: U2.26 (TXD), U14.34 (RXD0)
/UART0_TX: U2.25 (RXD), U14.35 (TXD0)
/VSENSE: R17.1, R18.2, U5.7 (VSENSE)
GND: C1.2, C2.2, C3.2, C4.2, C5.1, C6.1, C7.1, C8.1, C20.2, C21.2, C22.2, C23.2, C24.2, C25.2, C26.2, C27.2, C28.2, C29.2, C31.1, C32.1, C33.1, C36.1, C37.2, C41.2, C42.2, C43.2, C44.2, C48.2, C49.2, C50.2, C51.2, C69.2, D1.2 (GND), D2.2 (GND), D3.1 (K), J1.A1 (GND), J1.A12 (GND), J1.B1 (GND), J1.B12 (GND), J1.S1 (SHIELD), R3.1, R4.1, R6.1, R9.1, R15.1, R18.1, R19.1, R21.2, U1.3, U2.3 (GND), U2.29 (GND), U3.3 (GND), U3.5 (A0), U4.3 (GND), U5.2 (GND_2), U5.3 (GND_3), U5.15 (EXP), U6.2 (GND), U7.2 (-), U8.3, U9.3, U10.3, U12.3, U14.1 (GND), U14.15 (GND), U14.38 (GND), U14.39_1 (GND), U14.39_2 (GND), U14.39_3 (GND), U14.39_4 (GND), U14.39_5 (GND), U14.39_6 (GND), U14.39_7 (GND), U14.39_8 (GND), U14.39_9 (GND), U14.39_10 (GND), U14.39_11 (GND), U14.39_12 (GND), U14.39_13 (GND), U14.39_14 (GND), U14.39_15 (GND), U14.39_16 (GND)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
unnamed: C28.1, R16.1
unnamed: D1.1 (DO), D2.3 (DI)
unnamed: D3.2 (A), R12.1
unnamed: C20.1, C21.1, D4.1 (K), D5.1 (K), U6.1 (VIN), U6.3 (CE)
unnamed: J1.A5 (CC1), R4.2
unnamed: J1.B5 (CC2), R3.2
unnamed: Q2.1 (B), R10.2
unnamed: Q3.1 (B), R11.2
unnamed: F1.2, SW1.2 (B)
unnamed: R5.1, R6.2, U2.8 (VBUS)
unnamed: C3.1, C4.1, R8.1, U2.6 (VDD), U2.7 (VREGIN)
unnamed: R7.1, U2.9 (~RST)
unnamed: R9.2, U2.11 (~SUSPEND)
unnamed: R34.2, U3.9 (CRITICAL)
unnamed: C38.1, R22.2, U3.12 (IN+1)
unnamed: C39.1, R26.2, U3.15 (IN+2)
unnamed: C40.1, R29.2, U3.2 (IN+3)
unnamed: C38.2, R23.2, U3.11 (IN-1)
unnamed: C39.2, R27.2, U3.14 (IN-2)
unnamed: C40.2, R30.2, U3.1 (IN-3)
unnamed: R33.2, U3.10 (PV)
unnamed: R36.2, U3.13 (TC)
unnamed: R35.2, U3.8 (WARNING)
unnamed: R47.2, U4.9 (CRITICAL)
unnamed: C45.1, R40.2, U4.12 (IN+1)
unnamed: C46.1, R42.2, U4.15 (IN+2)
unnamed: C45.2, R41.2, U4.11 (IN-1)
unnamed: C46.2, R43.2, U4.14 (IN-2)
unnamed: R46.2, U4.10 (PV)
unnamed: R49.2, U4.13 (TC)
unnamed: R48.2, U4.8 (WARNING)
unnamed: C30.2, U5.13 (BOOT)
unnamed: C29.1, R16.2, U5.8 (COMP)
unnamed: R19.2, U5.1 (RT/CLK)
unnamed: C33.2, U5.9 (SS/TR)
VBUS: D5.2 (A), J1.A4 (VBUS), J1.A9 (VBUS), J1.B4 (VBUS), J1.B9 (VBUS), R5.2
VCC: C8.2, C26.1, C27.1, R13.2, SW1.3 (C), U5.4 (PVIN_4), U5.5 (PVIN_5), U5.6 (VIN)

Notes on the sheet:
CP2102 AUTO PROGRAM
Power
CURRENT
TYPEC
Driver Servo
MCU MAIN
LED

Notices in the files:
README.md:
License: GPL 3.0
